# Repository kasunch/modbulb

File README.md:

# modBulb - A modular light bulb for VLC
modBulb is an open source light bulb with a modular design that can be customized according to application’s requirements.
modBulb allows users to generate baseband signals simply through an MCU or an FPGA where more sophisticated signal processing is required. 
Moreover, modBulb offers the convenience of reprogramming the MCU and FPGA wirelessly to the users. 

modBulb uses an energy efficient switching LED driving circuitry which makes modBulb usable beyond prototyping and research applications.

## Hardware

modBulb hardware consists of three parts:

- Light source i.e. LEDs
- LED driver
- Baseband generator

There are two types of baseband generators:

- MCU baseband generator

  This baseband generator is built with TI's CC3200 SoC which is clocked at 80 MHz.

- FPGA baseband generator

  This baseband generator is built with Microsemi's AGLN060 FPGA which is clocked at 20 MHz.

Following figure shows the two baseband generators (top: FPGA baseband generator, middle MCU baseband generator) and the LED driver. 

Prototype Implementation

## Software

modBulb software undergoes a major restructuring  at the moment. However, the current software can be found in [github.com/modBulb/modBulb](https://github.com/modBulb/modBulb).

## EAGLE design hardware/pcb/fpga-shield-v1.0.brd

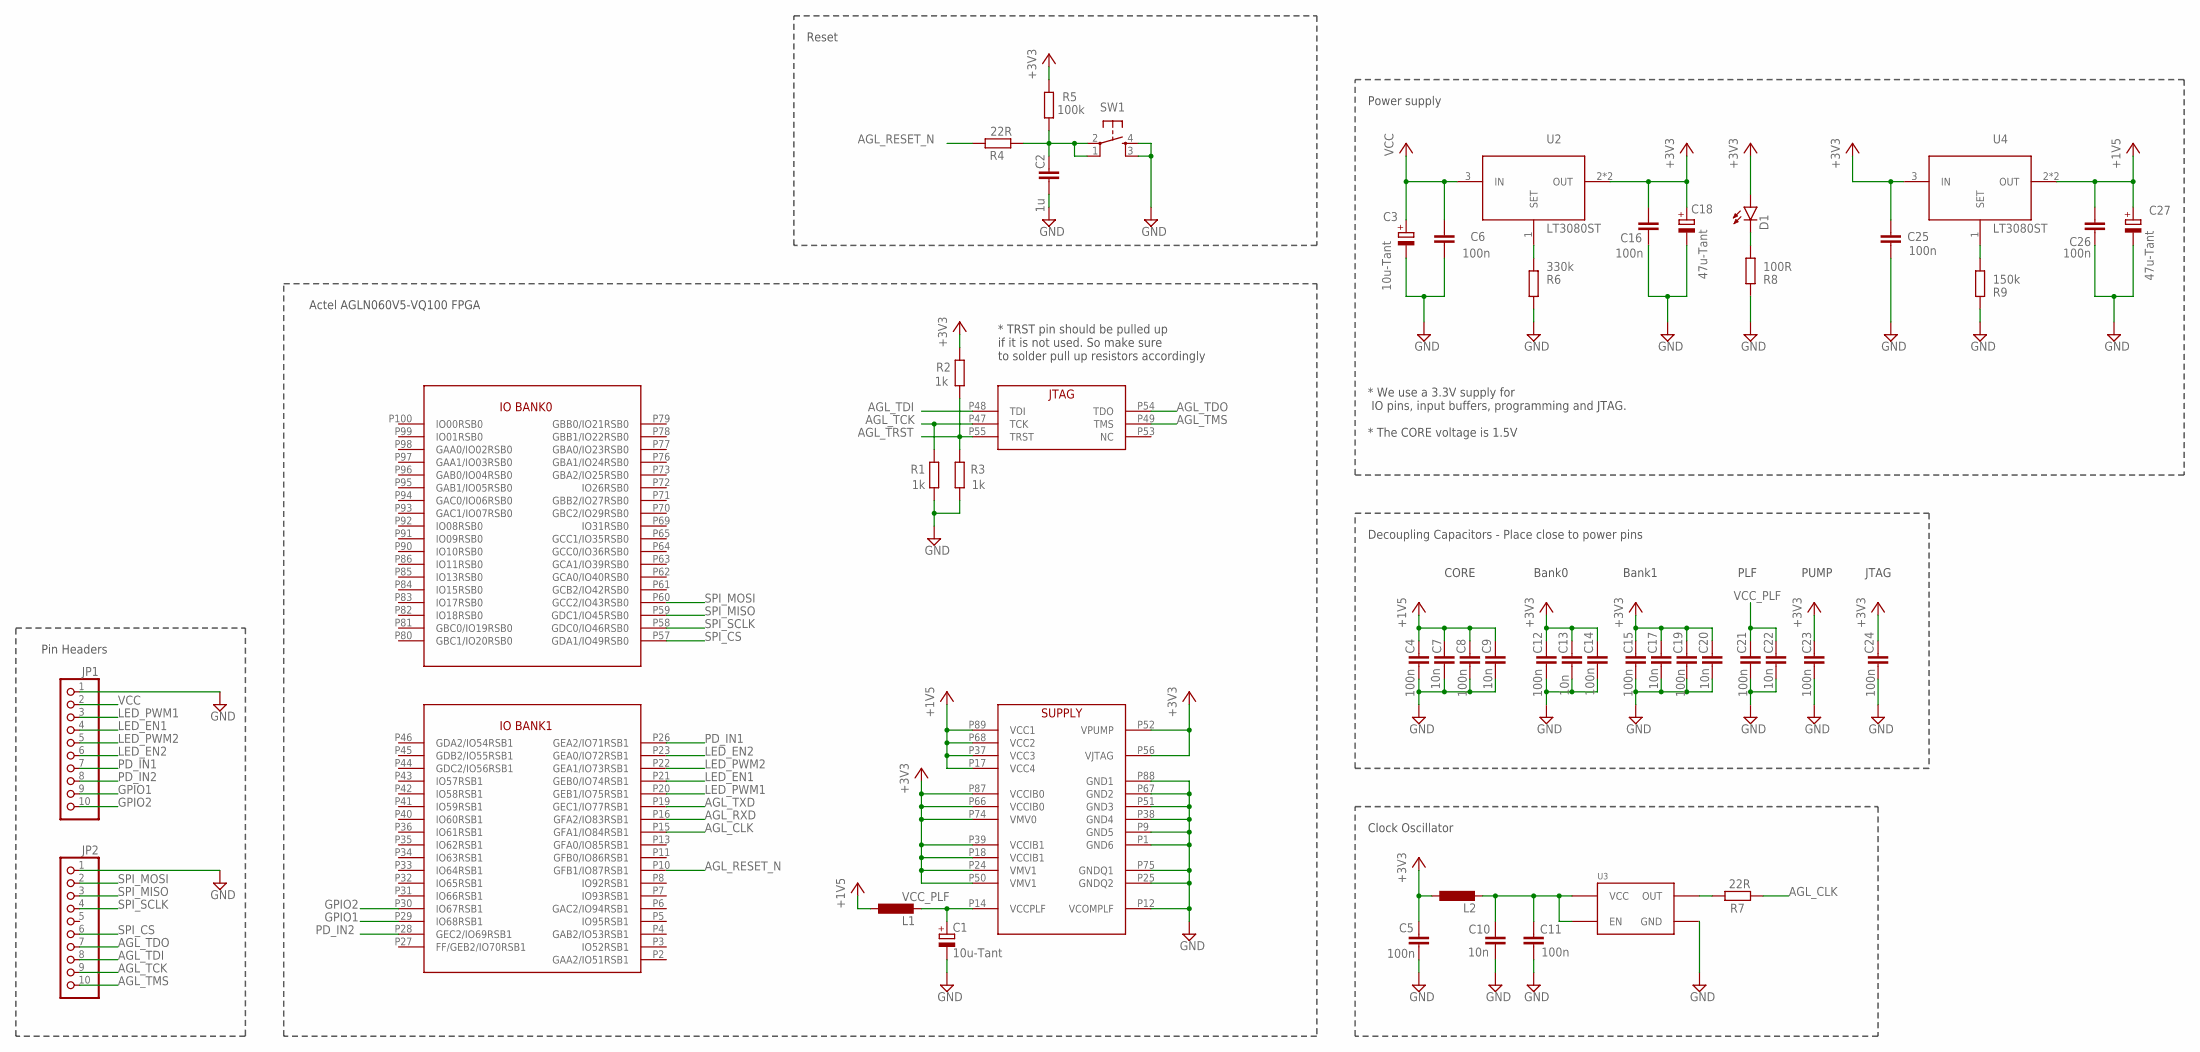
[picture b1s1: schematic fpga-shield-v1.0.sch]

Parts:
C1, C3: 10u-Tant; CT3528
C2: 1u; C0805
C4, C5, C6, C8, C11, C12, C14, C15, C16, C19, C21, C23, C24, C25, C26: 100n; C0805
C7, C9, C10, C13, C17, C20, C22: 10n; C0805
C18, C27: 47u-Tant; CT3528
D1: LED0603; LED-0603
JP1, JP2: PINHD-1X10; 1X10
L1, L2: L-EUL3216C; L3216C
R1, R2, R3: 1k; R0805
R4, R7: 22R; R0805
R5: 100k; R0805
R6: 330k; R0805
R8: 100R; R0805
R9: 150k; R0805
SW1: 10-XX4X4SMD; BT4X4
U1: AGLN060VQ100; VQ100
U2, U4: LT3080ST; SOT223
U3: ASFL1

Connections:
+1V5: C4.1, C7.1, C8.1, C9.1, C26.1, C27.+, L1.1, U1.P17 (VCC4), U1.P37 (VCC3), U1.P68 (VCC2), U1.P89 (VCC1), U4.2 (OUT), U4.4 (OUT)
+3V3: C5.1, C12.1, C13.1, C14.1, C15.1, C16.1, C17.1, C18.+, C19.1, C20.1, C23.1, C24.1, C25.1, D1.A, L2.1, R2.2, R5.2, U1.P18 (VCCIB1), U1.P24 (VMV1), U1.P39 (VCCIB1), U1.P50 (VMV1), U1.P52 (VPUMP), U1.P56 (VJTAG), U1.P66 (VCCIB0), U1.P74 (VMV0), U1.P87 (VCCIB0), U2.2 (OUT), U2.4 (OUT), U4.3 (IN)
AGL_CLK: R7.2, U1.P15 (GFA1/IO84RSB1)
AGL_RESET_N: R4.2, U1.P10 (GFB1/IO87RSB1)
AGL_RXD: U1.P16 (GFA2/IO83RSB1)
AGL_TCK: JP2.9, R1.2, U1.P47 (TCK)
AGL_TDI: JP2.8, U1.P48 (TDI)
AGL_TDO: JP2.7, U1.P54 (TDO)
AGL_TMS: JP2.10, U1.P49 (TMS)
AGL_TRST: R2.1, R3.2, U1.P55 (TRST)
AGL_TXD: U1.P19 (GEC1/IO77RSB1)
GND: C1.-, C2.2, C3.-, C4.2, C5.2, C6.2, C7.2, C8.2, C9.2, C10.2, C11.2, C12.2, C13.2, C14.2, C15.2, C16.2, C17.2, C18.-, C19.2, C20.2, C21.2, C22.2, C23.2, C24.2, C25.2, C26.2, C27.-, JP1.1, JP2.1, R1.1, R3.1, R6.2, R8.2, R9.2, SW1.3 (S1), SW1.4 (S), U1.P1 (GND6), U1.P9 (GND5), U1.P12 (VCOMPLF), U1.P25 (GNDQ2), U1.P38 (GND4), U1.P51 (GND3), U1.P67 (GND2), U1.P75 (GNDQ1), U1.P88 (GND1), U3.P$2 (GND)
GPIO1: JP1.9, U1.P29 (IO68RSB1)
GPIO2: JP1.10, U1.P30 (IO67RSB1)
LED_EN1: JP1.4, U1.P21 (GEB0/IO74RSB1)
LED_EN2: JP1.6, U1.P23 (GEA0/IO72RSB1)
LED_PWM1: JP1.3, U1.P20 (GEB1/IO75RSB1)
LED_PWM2: JP1.5, U1.P22 (GEA1/IO73RSB1)
unnamed: R7.1, U3.P$3 (OUT)
unnamed: C10.1, C11.1, L2.2, U3.P$1 (EN), U3.P$4 (VCC)
unnamed: D1.C, R8.1
unnamed: R6.1, U2.1 (SET)
unnamed: R9.1, U4.1 (SET)
unnamed: C2.1, R4.1, R5.1, SW1.1, SW1.2
PD_IN1: JP1.7, U1.P26 (GEA2/IO71RSB1)
PD_IN2: JP1.8, U1.P28 (GEC2/IO69RSB1)
SPI_CS: JP2.6, U1.P57 (GDA1/IO49RSB0)
SPI_MISO: JP2.3, U1.P59 (GDC1/IO45RSB0)
SPI_MOSI: JP2.2, U1.P60 (GCC2/IO43RSB0)
SPI_SCLK: JP2.4, U1.P58 (GDC0/IO46RSB0)
VCC: C3.+, C6.1, JP1.2, U2.3 (IN)
VCC_PLF: C1.+, C21.1, C22.1, L1.2, U1.P14 (VCCPLF)

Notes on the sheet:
* We use a 3.3V supply for IO pins, input buffers, programming and JTAG. * The CORE voltage is 1.5V
Decoupling Capacitors - Place close to power pins
CORE
Bank0
Bank1
PLF
PUMP
JTAG
* TRST pin should be pulled up if it is not used. So make sure to solder pull up resistors accordingly
Clock Oscillator
Power supply
Reset
Actel AGLN060V5-VQ100 FPGA
Pin Headers

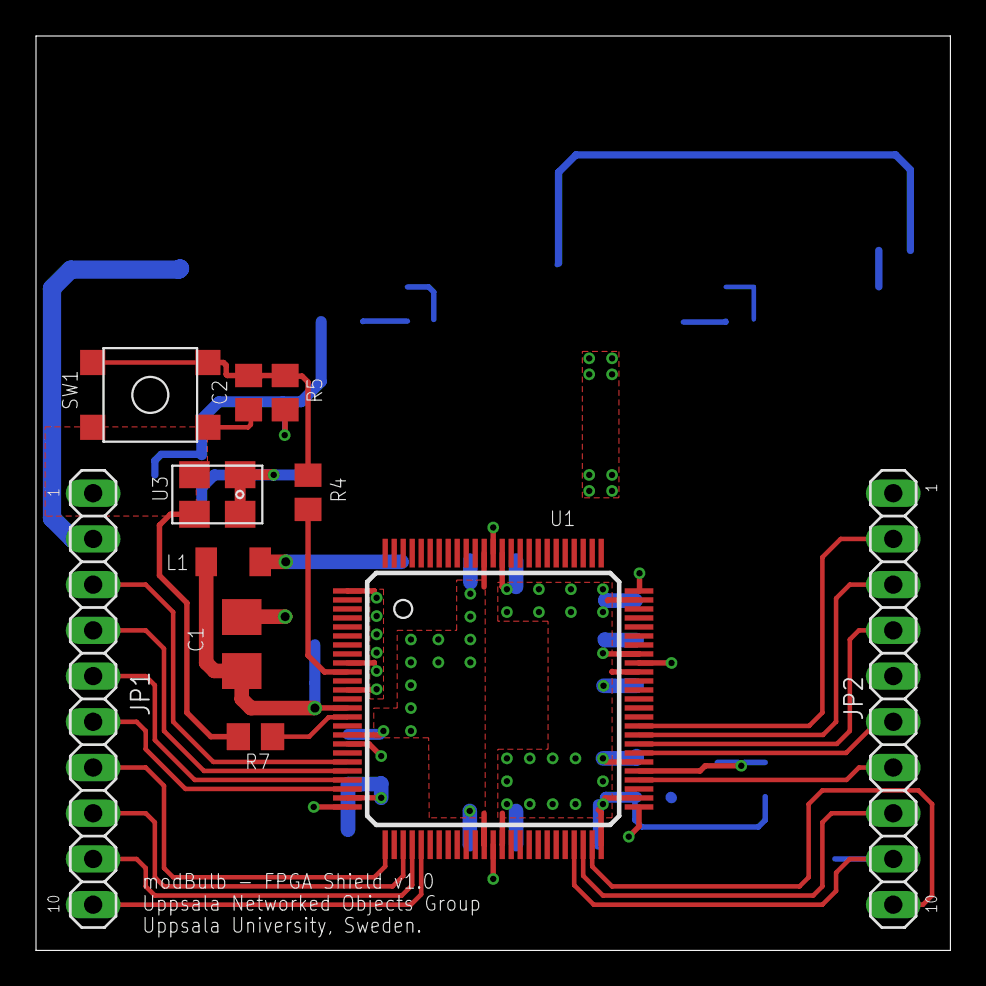
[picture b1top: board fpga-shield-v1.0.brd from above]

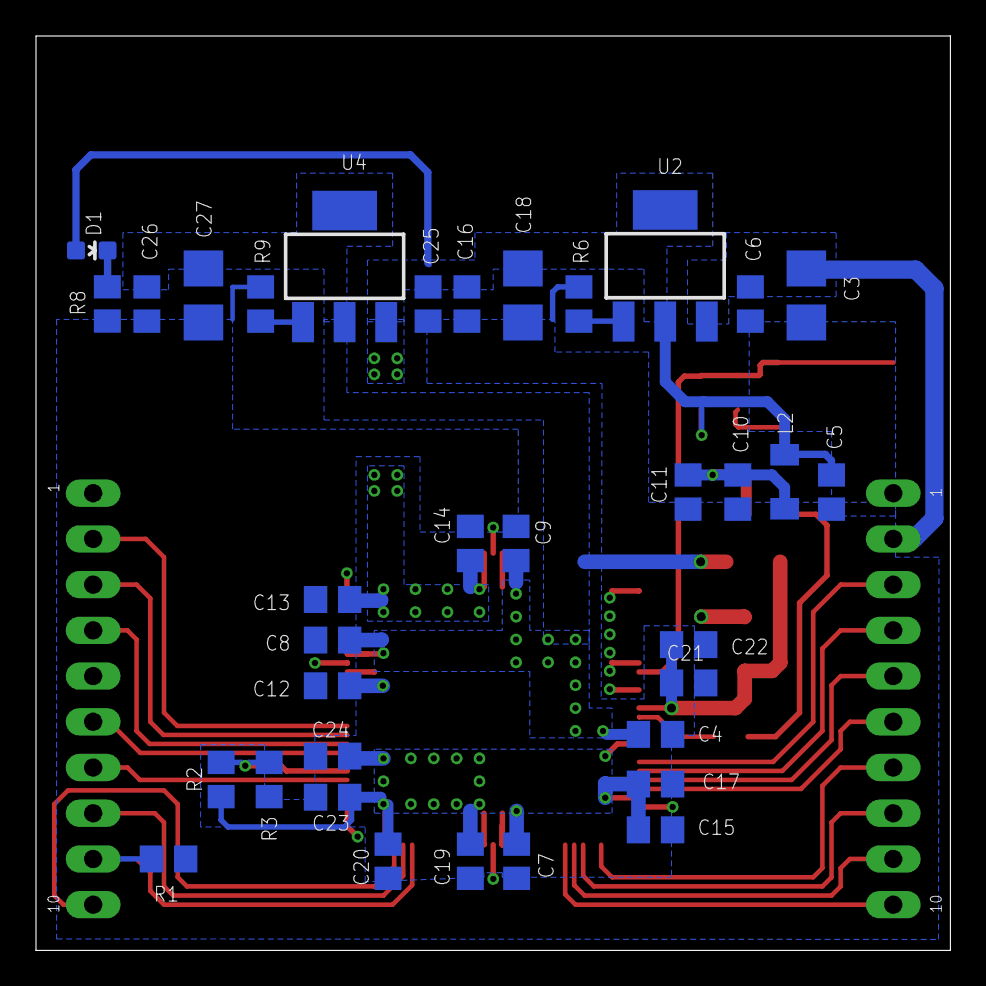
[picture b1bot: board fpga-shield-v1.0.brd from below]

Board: 2 copper layers, 50.8 x 50.8 mm, 46 parts (35 on the bottom side), 30 nets.

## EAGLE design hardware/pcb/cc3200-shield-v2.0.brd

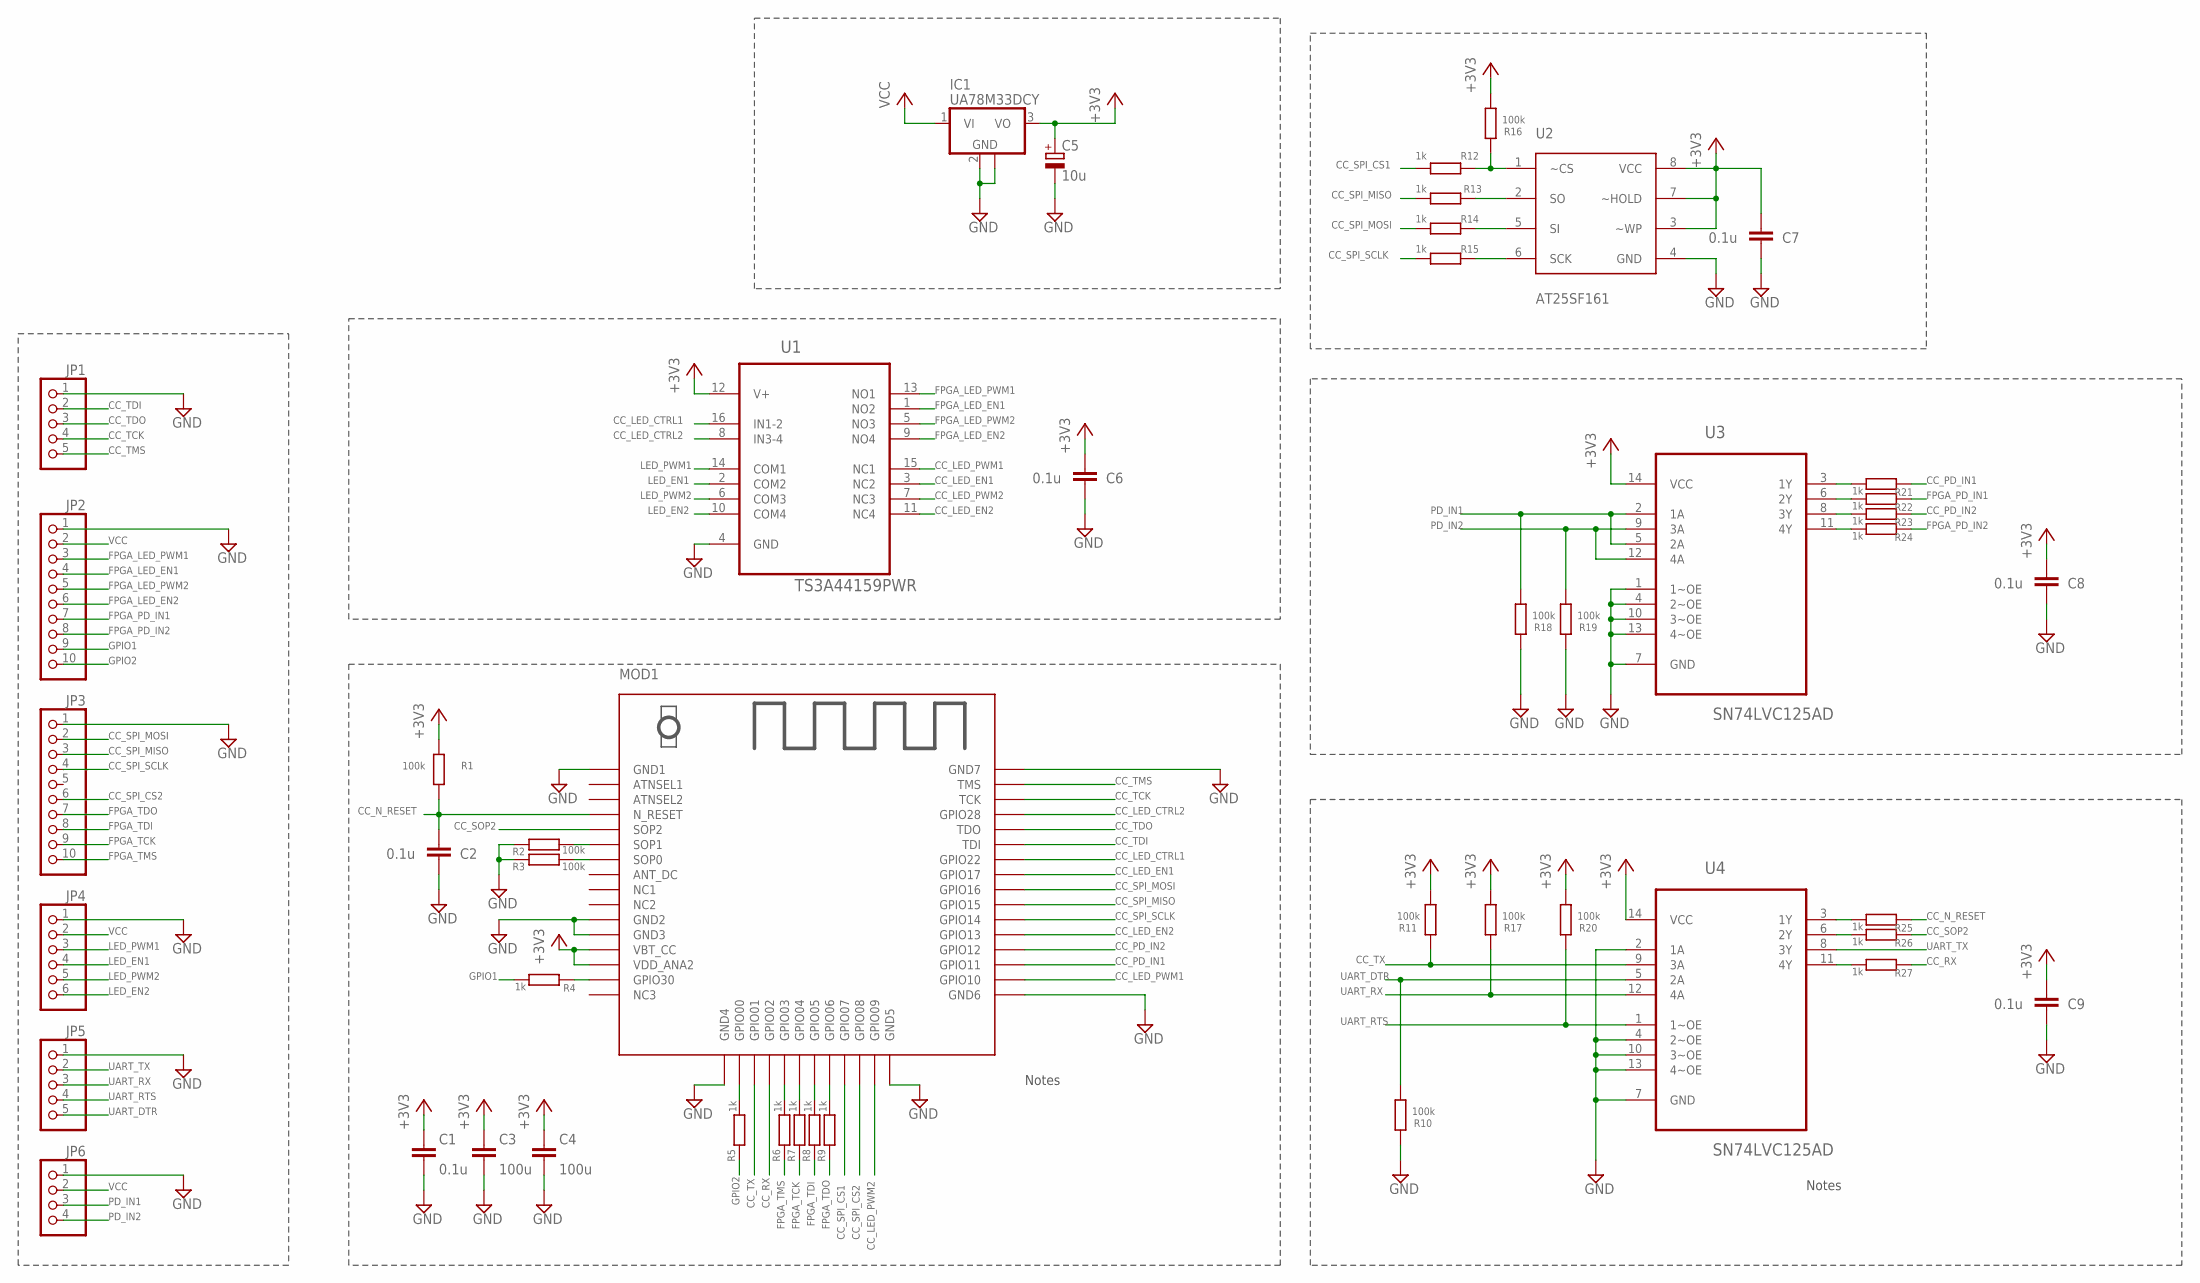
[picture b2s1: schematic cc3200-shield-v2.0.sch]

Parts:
C1, C2, C6, C7, C8, C9: 0.1u; C0805
C3, C4: 100u; C1210
C5: 10u; 153CLV-0405
IC1: UA78M33DCY; SOT223
JP1, JP5: PINHD-1X51X05-1.27MM; 1X05-1.27MM
JP2, JP3: PINHD-1X10; 1X10
JP4: PINHD-1X6; 1X06
JP6: PINHD-1X41.27MM; 1X04-1.27MM
MOD1: USR-C322
R1, R2, R3, R10, R11, R16, R17, R18, R19, R20: 100k; R0805
R4, R5, R6, R7, R8, R9, R12, R13, R14, R15, R21, R22, R23, R24, R25, R26, R27: 1k; R0805
U1: TS3A44159PWR; SOP65P640X120-16N
U2: AT25SF161; SO08
U3, U4: SN74LVC125AD; SOIC127P600X175-14N

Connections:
+3V3: C1.1, C3.1, C4.1, C5.+, C6.1, C7.1, C8.1, C9.1, IC1.3 (VO), MOD1.VBT_CC, MOD1.VDD_ANT (VDD_ANA2), R1.2, R11.2, R16.2, R17.2, R20.2, U1.12 (V+), U2.3 (~WP), U2.7 (~HOLD), U2.8 (VCC), U3.14 (VCC), U4.14 (VCC)
CC_LED_CTRL1: MOD1.GPIO22, U1.16 (IN1-2)
CC_LED_CTRL2: MOD1.GPIO28, U1.8 (IN3-4)
CC_LED_EN1: MOD1.GPIO17, U1.3 (NC2)
CC_LED_EN2: MOD1.GPIO13, U1.11 (NC4)
CC_LED_PWM1: MOD1.GPIO10, U1.15 (NC1)
CC_LED_PWM2: MOD1.GPIO09, U1.7 (NC3)
CC_N_RESET: C2.1, MOD1.N_RESET, R1.1, R25.1
CC_PD_IN1: MOD1.GPIO11, R21.1
CC_PD_IN2: MOD1.GPIO12, R23.1
CC_RX: MOD1.GPIO02, R27.1
CC_SOP2: MOD1.SOP2, R26.1
CC_SPI_CS1: MOD1.GPIO07, R12.2
CC_SPI_CS2: JP3.6, MOD1.GPIO08
CC_SPI_MISO: JP3.3, MOD1.SPI_MISO/GPIO15 (GPIO15), R13.2
CC_SPI_MOSI: JP3.2, MOD1.GPIO16, R14.2
CC_SPI_SCLK: JP3.4, MOD1.GPIO14, R15.2
CC_TCK: JP1.4, MOD1.TCK
CC_TDI: JP1.2, MOD1.TDI
CC_TDO: JP1.3, MOD1.TDO
CC_TMS: JP1.5, MOD1.TMS
CC_TX: MOD1.GPIO01, R11.1, U4.9 (3A)
FPGA_LED_EN1: JP2.4, U1.1 (NO2)
FPGA_LED_EN2: JP2.6, U1.9 (NO4)
FPGA_LED_PWM1: JP2.3, U1.13 (NO1)
FPGA_LED_PWM2: JP2.5, U1.5 (NO3)
FPGA_PD_IN1: JP2.7, R22.1
FPGA_PD_IN2: JP2.8, R24.1
FPGA_TCK: JP3.9, R7.1
FPGA_TDI: JP3.8, R8.1
FPGA_TDO: JP3.7, R9.1
FPGA_TMS: JP3.10, R6.1
GND: C1.2, C2.2, C3.2, C4.2, C5.-, C6.2, C7.2, C8.2, C9.2, IC1.2 (GND), IC1.4 (GND), JP1.1, JP2.1, JP3.1, JP4.1, JP5.1, JP6.1, MOD1.GND1, MOD1.GND2, MOD1.GND3, MOD1.GND4, MOD1.GND5, MOD1.GND6, MOD1.GND7, R2.1, R3.1, R10.1, R18.1, R19.1, U1.4 (GND), U2.4 (GND), U3.1 (1~OE), U3.4 (2~OE), U3.7 (GND), U3.10 (3~OE), U3.13 (4~OE), U4.2 (1A), U4.4 (2~OE), U4.7 (GND), U4.10 (3~OE), U4.13 (4~OE)
GPIO1: JP2.9, R4.2
GPIO2: JP2.10, R5.1
LED_EN1: JP4.4, U1.2 (COM2)
LED_EN2: JP4.6, U1.10 (COM4)
LED_PWM1: JP4.3, U1.14 (COM1)
LED_PWM2: JP4.5, U1.6 (COM3)
unnamed: MOD1.SOP1, R2.2
unnamed: MOD1.SOP0, R3.2
unnamed: MOD1.GPIO00, R5.2
unnamed: MOD1.GPIO30, R4.1
unnamed: MOD1.GPIO03, R6.2
unnamed: MOD1.GPIO04, R7.2
unnamed: MOD1.GPIO05, R8.2
unnamed: MOD1.GPIO06, R9.2
unnamed: R25.2, U4.3 (1Y)
unnamed: R26.2, U4.6 (2Y)
unnamed: R27.2, U4.11 (4Y)
unnamed: R12.1, R16.1, U2.1 (~CS)
unnamed: R21.2, U3.3 (1Y)
unnamed: R22.2, U3.6 (2Y)
unnamed: R23.2, U3.8 (3Y)
unnamed: R24.2, U3.11 (4Y)
unnamed: R13.1, U2.2 (SO)
unnamed: R14.1, U2.5 (SI)
unnamed: R15.1, U2.6 (SCK)
PD_IN1: JP6.3, R18.2, U3.2 (1A), U3.5 (2A)
PD_IN2: JP6.4, R19.2, U3.9 (3A), U3.12 (4A)
UART_DTR: JP5.5, R10.2, U4.5 (2A)
UART_RTS: JP5.4, R20.1, U4.1 (1~OE)
UART_RX: JP5.3, R17.1, U4.12 (4A)
UART_TX: JP5.2, U4.8 (3Y)
VCC: IC1.1 (VI), JP2.2, JP4.2, JP6.2

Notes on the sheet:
Notes

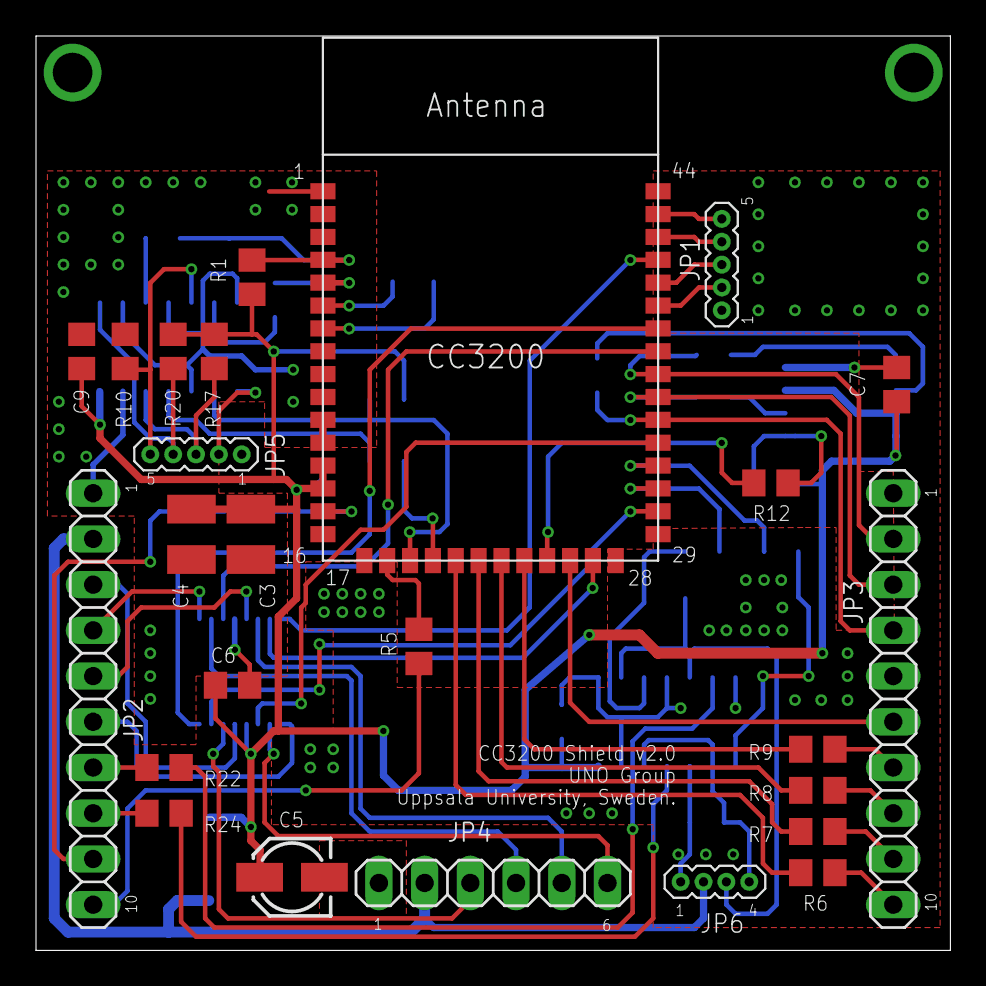
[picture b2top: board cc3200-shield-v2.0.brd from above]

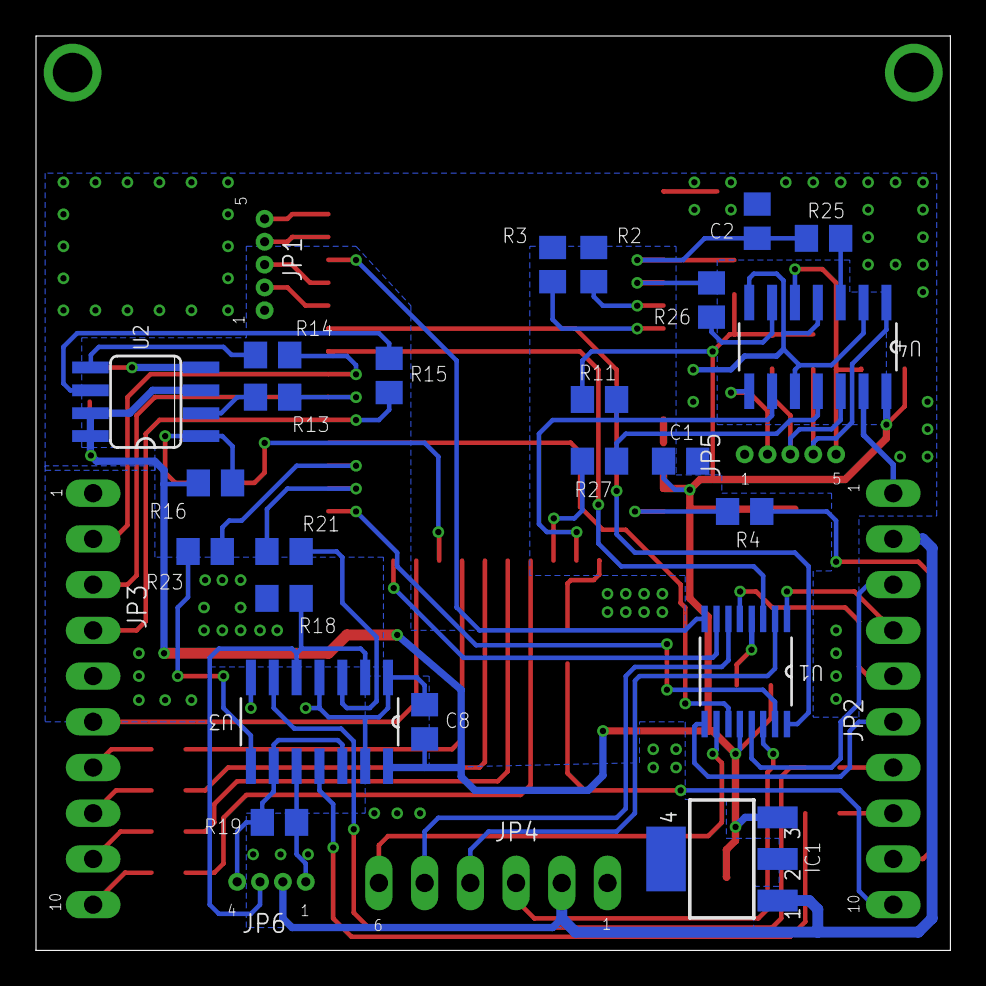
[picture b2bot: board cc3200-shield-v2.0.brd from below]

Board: 2 copper layers, 50.8 x 50.8 mm, 48 parts (23 on the bottom side), 65 nets.

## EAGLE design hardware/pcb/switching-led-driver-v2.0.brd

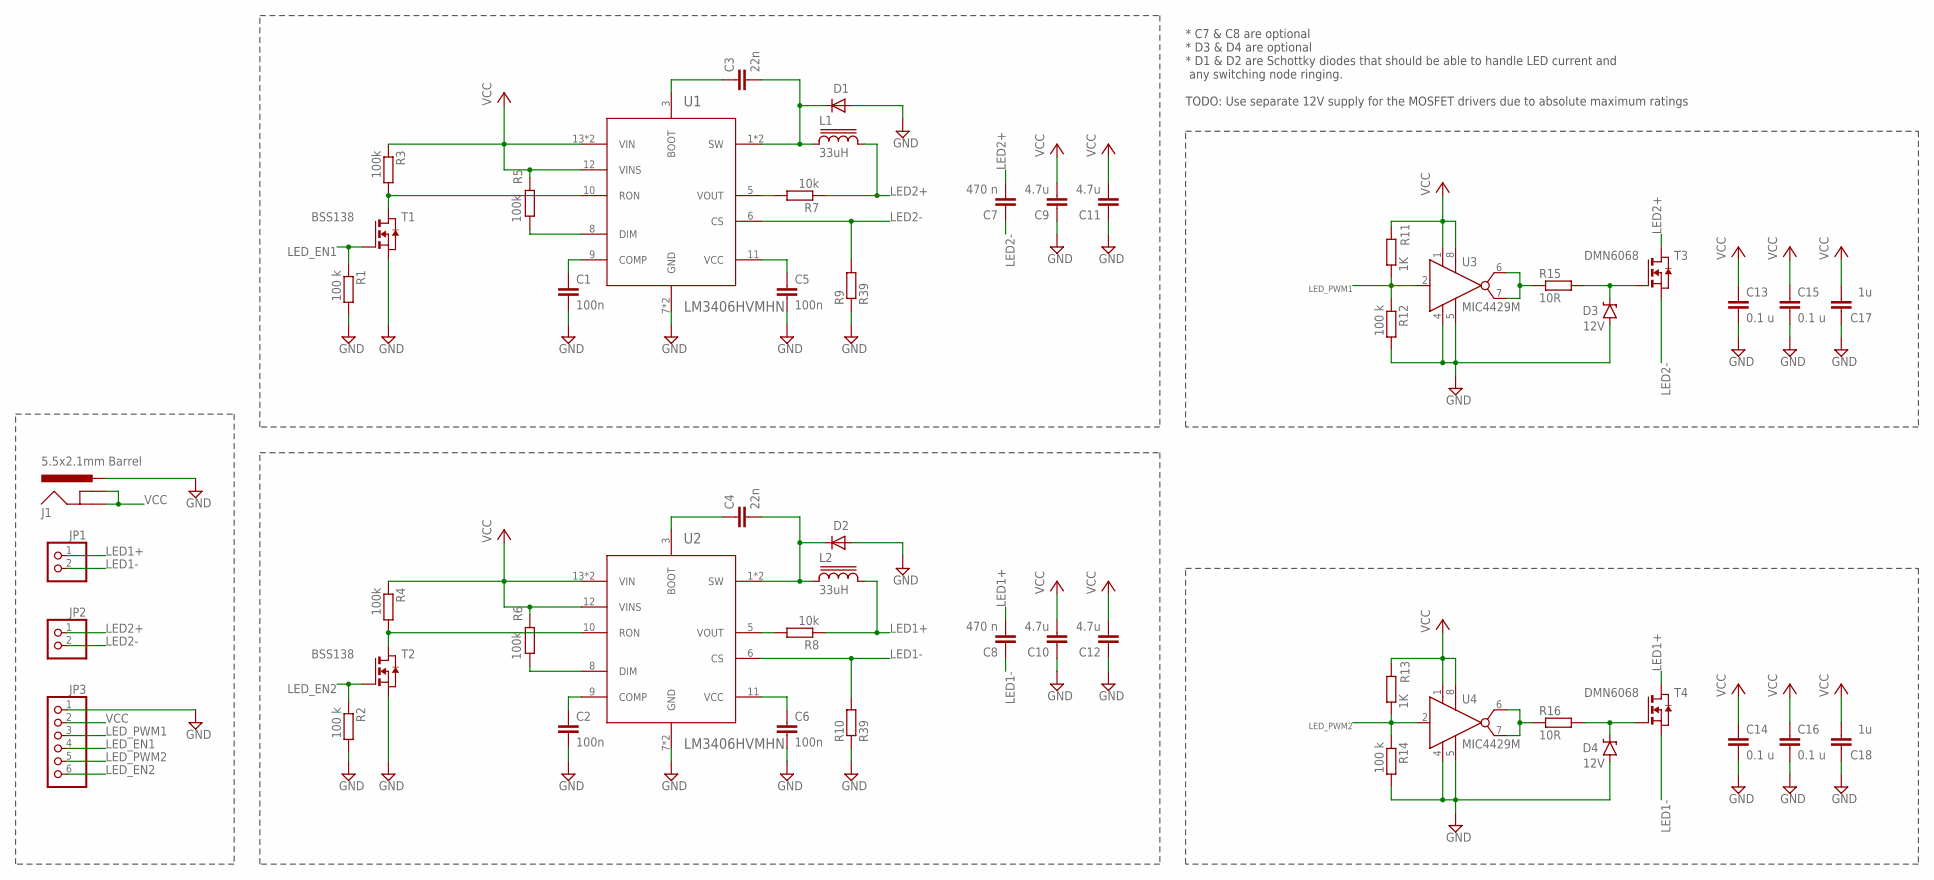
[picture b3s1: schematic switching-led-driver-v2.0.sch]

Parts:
C1, C2, C5, C6: 100n; C0805
C3, C4: 22n; C1206
C7, C8: 470 n; C1206
C9, C10, C11, C12: 4.7u; C1210
C13, C14, C15, C16: 0.1 u; C0805
C17, C18: 1u; C1210
D1, D2: 12V; DO-214AC
D3, D4: 12V; SOD-123
J1: 5.5x2.1mm Barrel; POWER_JACK_SMD
JP1, JP2: PINHD-1X2; 1X02
JP3: PINHD-1X6; 1X06
L1, L2: 33uH; SRR1260
R1, R2, R12, R14: 100 k; R0805
R3, R4, R5, R6: 100k; R0805
R7, R8: 10k; R0805
R9, R10: R39; R1206
R11, R13: 1K; R0805
R15, R16: 10R; R0805
T1, T2: BSS138; SOT-23
T3, T4: DMN6068; SOT223
U1, U2: LM3406HVMHN; HTSSOP-14-NN
U3, U4: MIC4429M; SO08

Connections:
GND: C1.2, C2.2, C5.2, C6.2, C9.1, C10.1, C11.1, C12.1, C13.2, C14.2, C15.2, C16.2, C17.1, C18.1, D1.A, D2.A, D3.A, D4.A, J1.VIN0 (PWR), JP3.1, R1.2, R2.2, R9.1, R10.1, R12.2, R14.2, T1.2 (S), T2.2 (S), U1.7 (GND), U1.15 (GND), U2.7 (GND), U2.15 (GND), U3.4 (GND1), U3.5 (GND2), U4.4 (GND1), U4.5 (GND2)
LED1+: C8.2, JP1.1, L2.2, R8.1, T4.2 (D), T4.4 (D)
LED1-: C8.1, JP1.2, R10.2, T4.3 (S), U2.6 (CS)
LED2+: C7.2, JP2.1, L1.2, R7.1, T3.2 (D), T3.4 (D)
LED2-: C7.1, JP2.2, R9.2, T3.3 (S), U1.6 (CS)
LED_EN1: JP3.4, R1.1, T1.3 (G)
LED_EN2: JP3.6, R2.1, T2.3 (G)
LED_PWM1: JP3.3, R11.1, R12.1, U3.2 (IN)
LED_PWM2: JP3.5, R13.1, R14.1, U4.2 (IN)
unnamed: R4.2, T2.1 (D), U2.10 (RON)
unnamed: C2.1, U2.9 (COMP)
unnamed: C6.1, U2.11 (VCC)
unnamed: R16.1, U4.6 (OUT1), U4.7 (OUT2)
unnamed: R8.2, U2.5 (VOUT)
unnamed: D3.C, R15.2, T3.1 (G)
unnamed: D4.C, R16.2, T4.1 (G)
unnamed: R3.2, T1.1 (D), U1.10 (RON)
unnamed: C1.1, U1.9 (COMP)
unnamed: C5.1, U1.11 (VCC)
unnamed: C3.1, U1.3 (BOOT)
unnamed: C4.1, U2.3 (BOOT)
unnamed: R7.2, U1.5 (VOUT)
unnamed: R15.1, U3.6 (OUT1), U3.7 (OUT2)
PWM_IN_INT: R6.1, U2.8 (DIM)
PWM_IN_INT1: R5.1, U1.8 (DIM)
SW: C4.2, D2.C, L2.1, U2.1 (SW), U2.2 (SW)
SW1: C3.2, D1.C, L1.1, U1.1 (SW), U1.2 (SW)
VCC: C9.2, C10.2, C11.2, C12.2, C13.1, C14.1, C15.1, C16.1, C17.2, C18.2, J1.GND (GNDBREAK), J1.P$4 (GND), JP3.2, R3.1, R4.1, R5.2, R6.2, R11.2, R13.2, U1.12 (VINS), U1.13 (VIN), U1.14 (VIN), U2.12 (VINS), U2.13 (VIN), U2.14 (VIN), U3.1 (VS1), U3.8 (VS2), U4.1 (VS1), U4.8 (VS2)

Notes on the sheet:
* C7 & C8 are optional * D3 & D4 are optional * D1 & D2 are Schottky diodes that should be able to handle LED current and any switching node ringing. TODO: Use separate 12V supply for the MOSFET drivers due to absolute maximum ratings

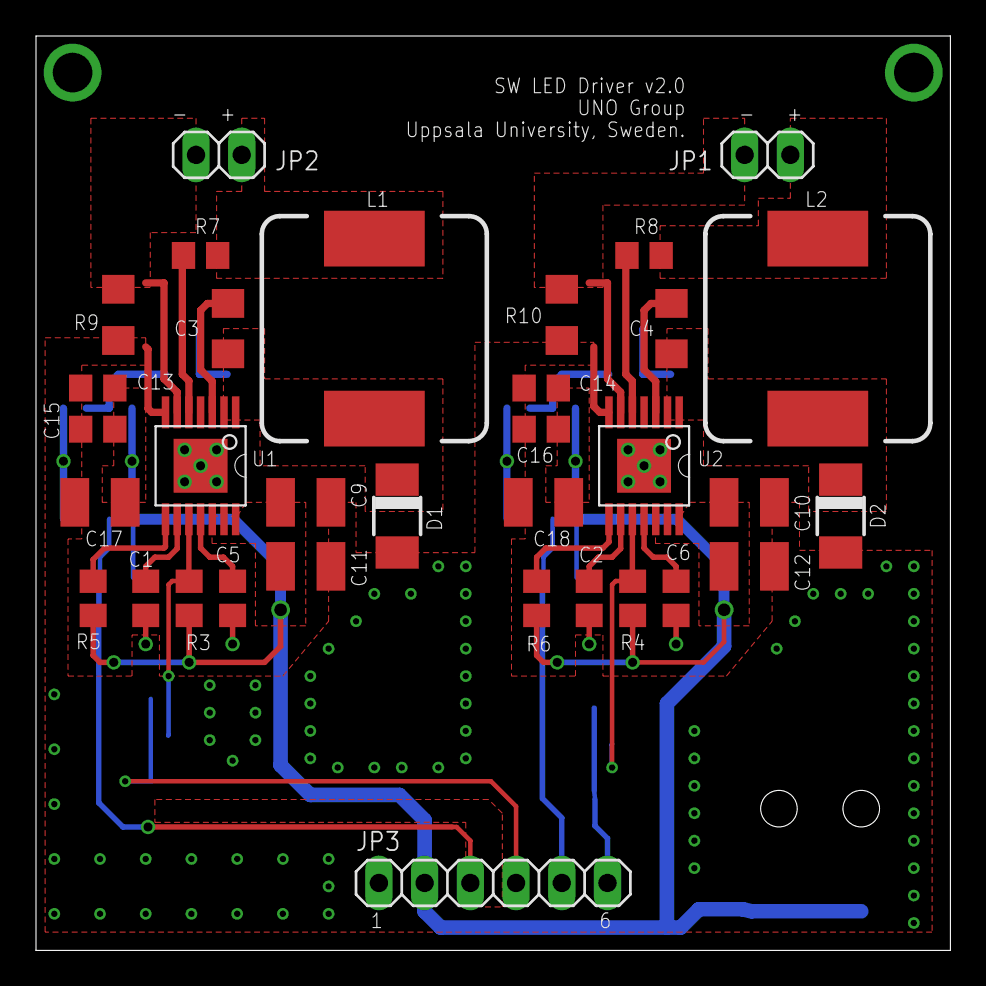
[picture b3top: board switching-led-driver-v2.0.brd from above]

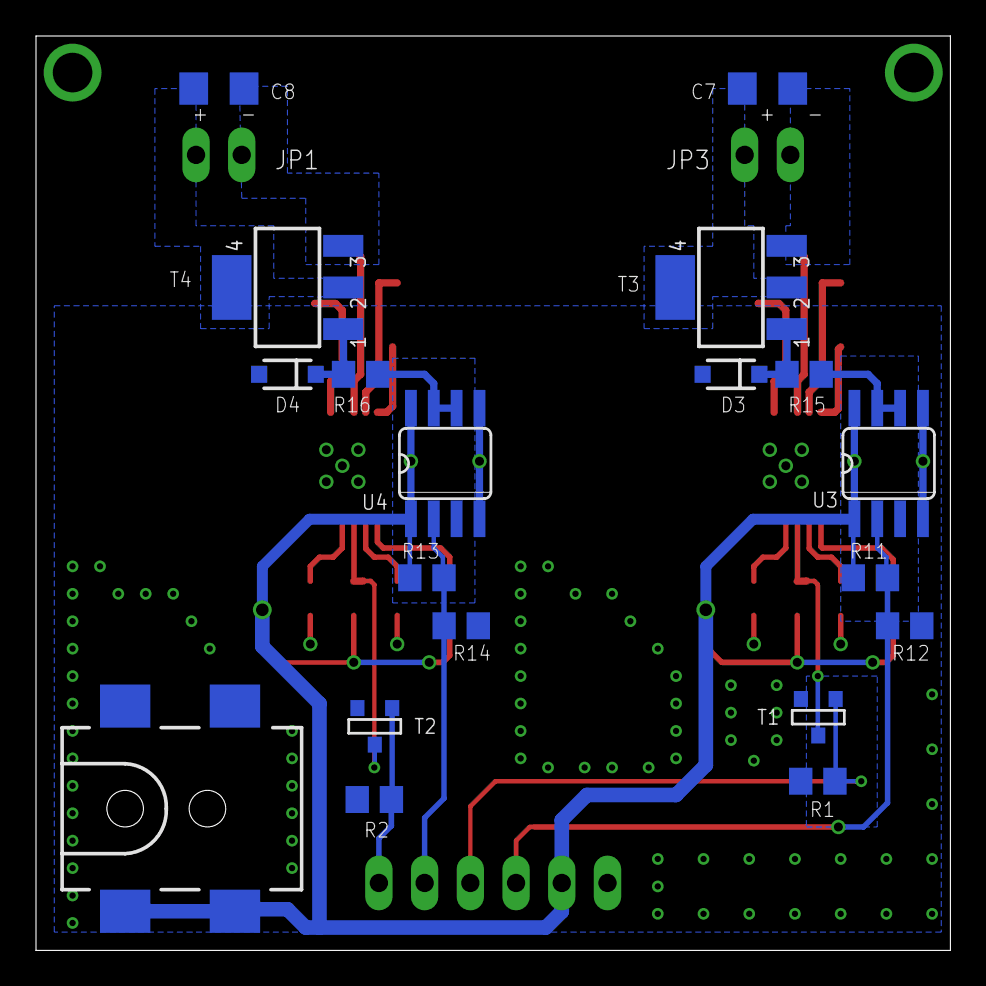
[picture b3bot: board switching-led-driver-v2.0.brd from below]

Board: 2 copper layers, 50.8 x 50.8 mm, 52 parts (19 on the bottom side), 28 nets.

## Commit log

2017-10-23 Adding PCBs and 3D model of the enclosure
2017-10-23 Resize image
2017-10-23 Added more details

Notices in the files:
parts and their libraries:
sparkfun-misc-parts-1: Licensing: Creative Commons ShareAlike 4.0 International - https://creativecommons.org/licenses/by-sa/4.0
inductor-bourns: Copyright (C) 2008, Bob Starr
